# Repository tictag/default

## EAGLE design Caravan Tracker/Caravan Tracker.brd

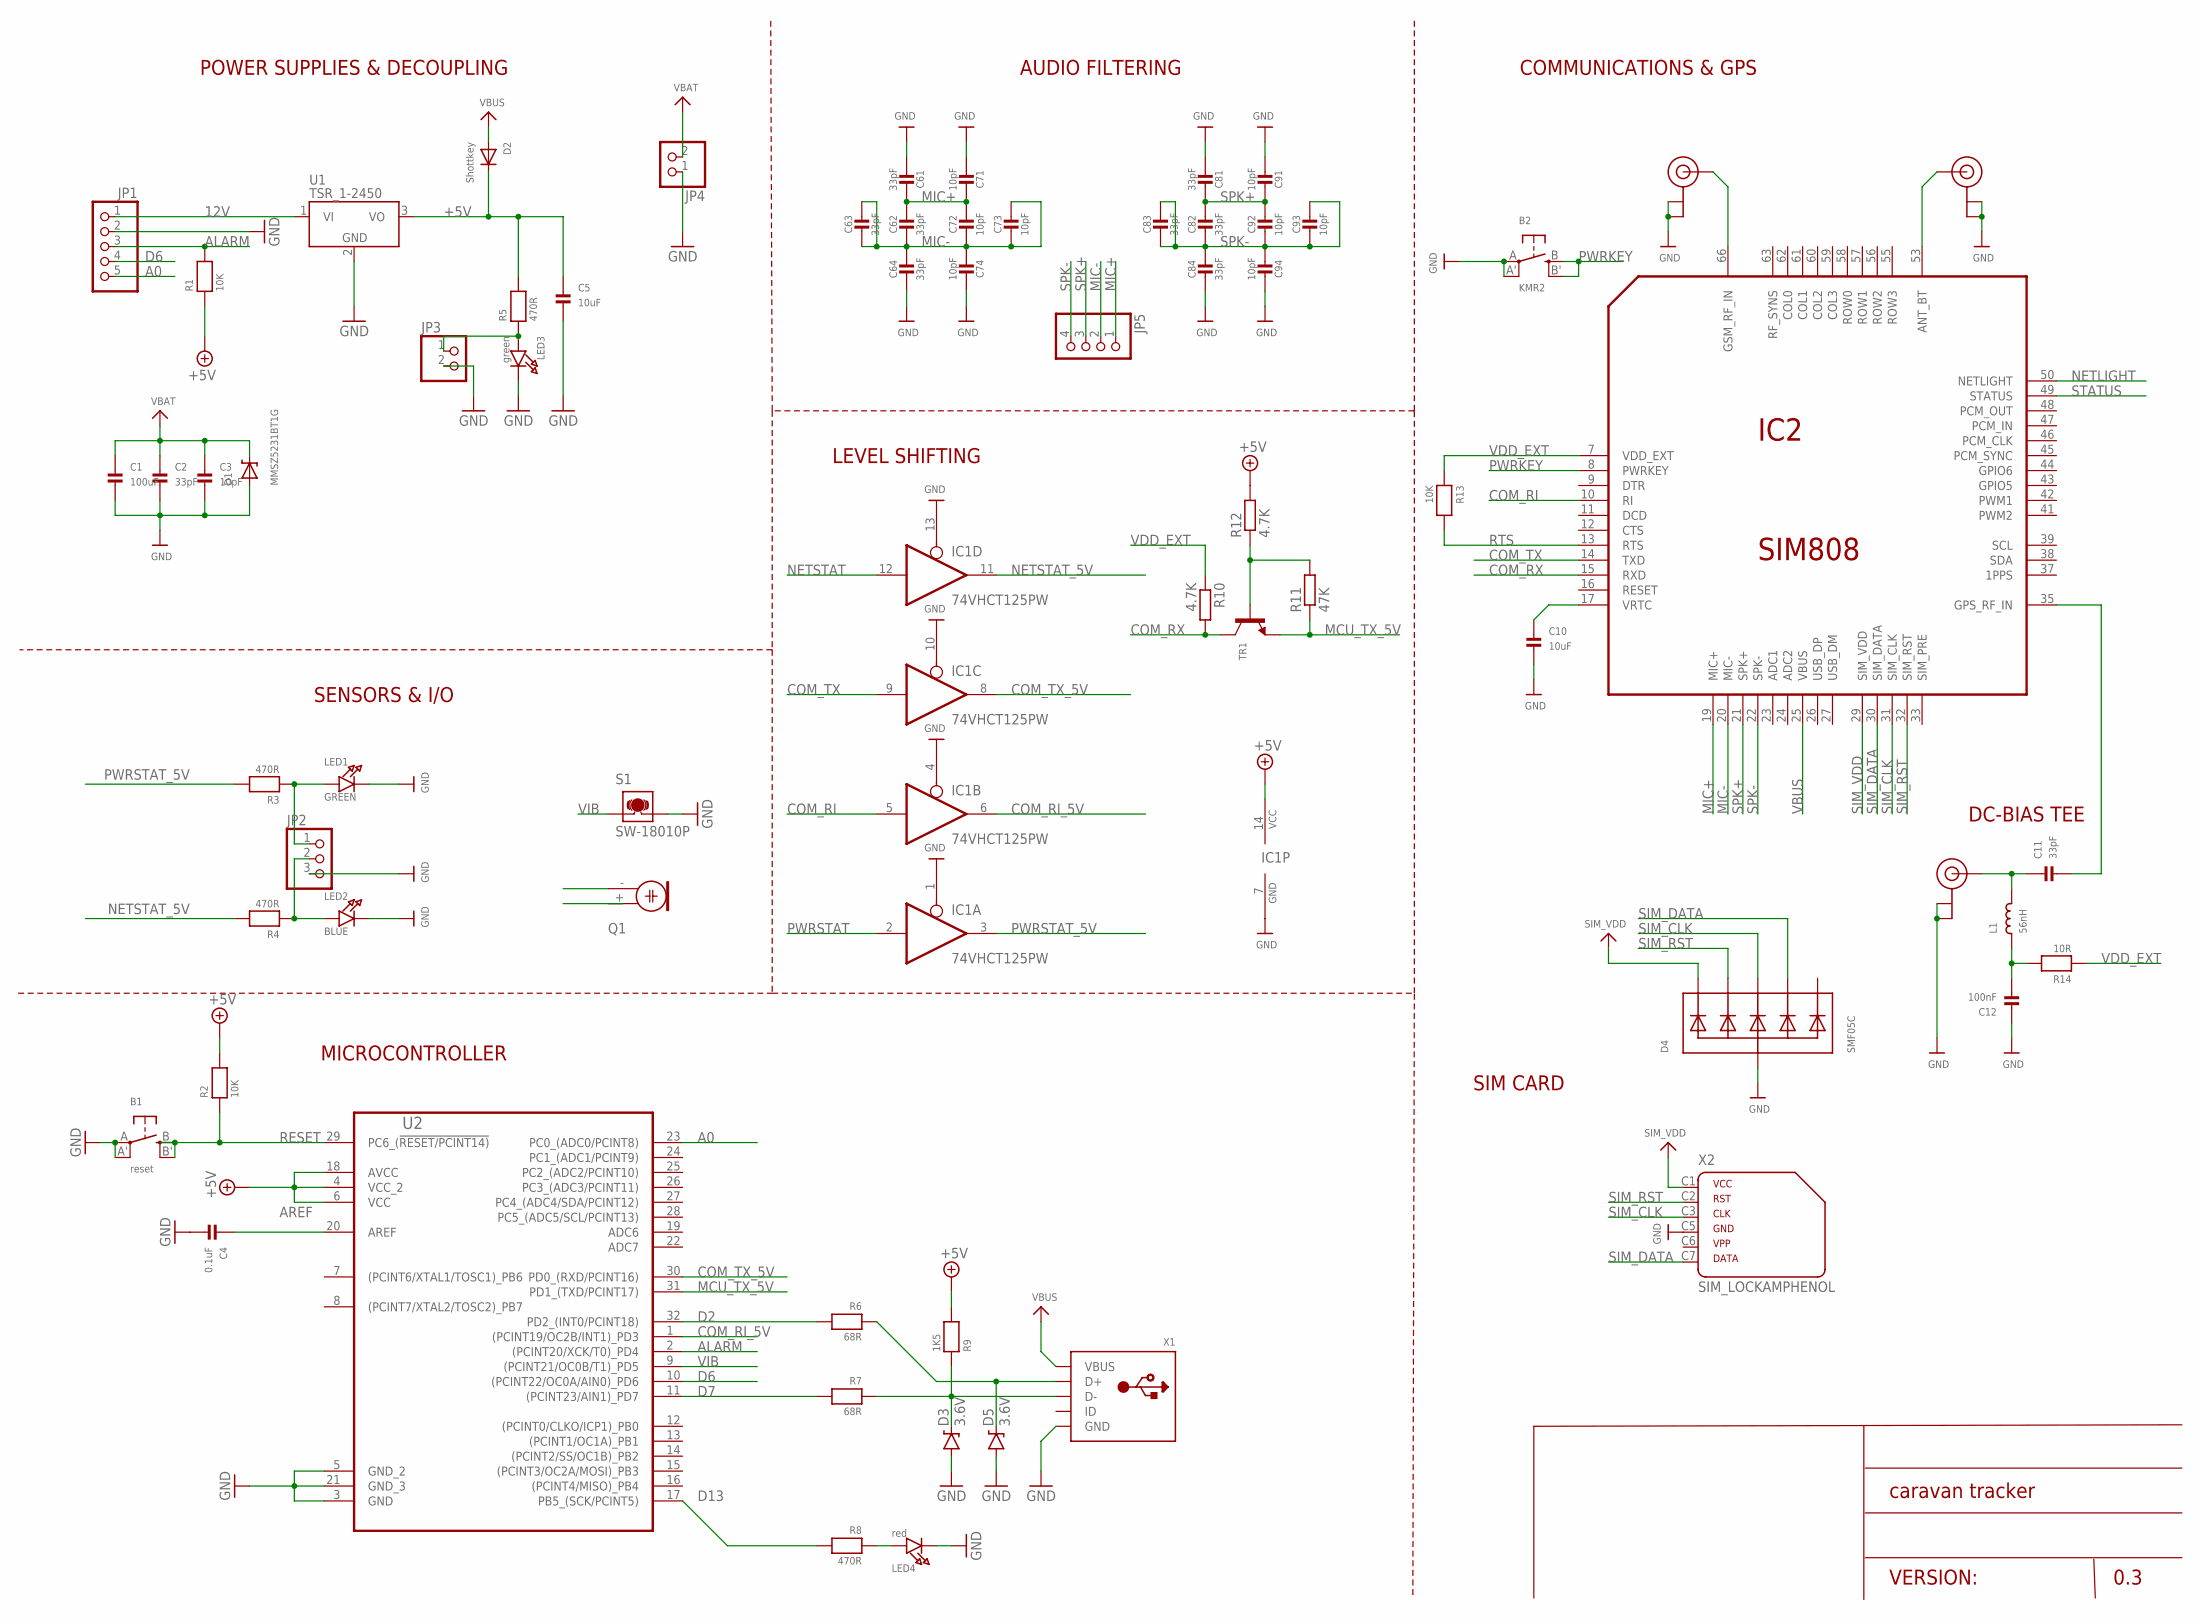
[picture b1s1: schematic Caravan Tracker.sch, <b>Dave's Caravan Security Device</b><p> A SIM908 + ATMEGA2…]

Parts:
B1: reset; BTN_KMR2_4.6X2.8
B2: KMR2; BTN_KMR2_4.6X2.8
C1: 100uF; 1206
C2, C11: 33pF; 0805
C3: 10pF; 0805
C4: 0.1uF; 0603
C5: 10uF; 0603
C6, C8: 33pF; RESPACK_4X0603
C7, C9: 10pF; RESPACK_4X0603
C10: 10uF; 0805
C12: 100nF; 0805
D1: MMSZ5231BT1G; SOD-123
D2: Shottkey; SOD-123
D3, D5: 3.6V; SOD-323
D4: SMF05C; SOT363
IC1: 74VHCT125PW; TSSOP14
IC2: SIM808
JP1: HEADER-1X5ROUND; 1X05_ROUND
JP2: HEADER-1X3ROUND; 1X03_ROUND
JP3: HEADER-1X2ROUND; 1X02_ROUND
JP4: JST_2PIN; JSTPH2
JP5: HEADER-1X4ROUND; 1X04_ROUND
L1: 56nH; _0805
LED1: GREEN; CHIPLED_0805_NOOUTLINE
LED2: BLUE; CHIPLED_0805_NOOUTLINE
LED3: green; CHIPLED_0805_NOOUTLINE
LED4: red; CHIPLED_0805_NOOUTLINE
Q1: ELECTRET; 9.7ELECTRET
R1, R2, R13: 10K; 0603
R3, R4, R5, R8: 470R; 0603
R6, R7: 68R; 0603
R9: 1K5; 0603
R10, R12: 4.7K; R0603
R11: 47K; R0603
R14: 10R; _0805
S1: SW-18010P
TR1: TRANSISTOR_NPN; SOT23-R
U1: TSR_1-2450; TSR-1
U2: ATMEGA328-AU; QFP80P900X900X120-32N
U$1: U.FL (GPS); U.FL
U$2, U$3: U.FL
X1: USBMICRO_20329; 4UCONN_20329
X2: SIM_LOCKAMPHENOL; C707_10M006_512_2

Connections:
12V: JP1.1, U1.1 (VI)
+5V: C5.1, D2.C, IC1.14 (VCC), R1.1, R2.2, R5.2, R9.2, R12.2, U1.3 (VO), U2.4 (VCC_2), U2.6 (VCC), U2.18 (AVCC)
A0: JP1.5, U2.23 (PC0_(ADC0/PCINT8))
ALARM: JP1.3, R1.2, U2.2 ((PCINT20/XCK/T0)_PD4)
ANT_BT: IC2.53 (ANT_BT), U$3.3 (SIGNAL)
AREF: C4.1, U2.20 (AREF)
COM_RI: IC1.5 (I), IC2.10 (RI)
COM_RI_5V: IC1.6 (O), U2.1 ((PCINT19/OC2B/INT1)_PD3)
COM_RX: IC2.15 (RXD), R10.2, TR1.3 (C)
COM_TX: IC1.9 (I), IC2.14 (TXD)
COM_TX_5V: IC1.8 (O), U2.30 (PD0_(RXD/PCINT16))
D2: R6.2, U2.32 (PD2_(INT0/PCINT18))
D6: JP1.4, U2.10 ((PCINT22/OC0A/AIN0)_PD6)
D7: R7.2, U2.11 ((PCINT23/AIN1)_PD7)
D13: R8.2, U2.17 (PB5_(SCK/PCINT5))
GND: B1.A, B1.A' (P1), B2.A, B2.A' (P1), C1.2, C2.2, C3.2, C4.2, C5.2, C6.5 (2), C6.8 (2), C7.4 (1), C7.8 (2), C8.5 (2), C8.8 (2), C9.4 (1), C9.8 (2), C10.2, C12.1, D1.A, D3.A, D4.2 (A), D5.A, IC1.1 (OE), IC1.4 (OE), IC1.7 (GND), IC1.10 (OE), IC1.13 (OE), IC2.1 (GND), IC2.2 (GND), IC2.3 (GND), IC2.18 (GND), IC2.28 (GND), IC2.34 (GND), IC2.36 (GND), IC2.40 (GND), IC2.51 (GND), IC2.52 (GND), IC2.54 (GND), IC2.64 (GND), IC2.65 (GND), IC2.67 (GND), IC2.68 (GND), JP1.2, JP2.3, JP3.2, JP4.1, LED1.C, LED2.C, LED3.C, LED4.C, S1.1, U1.2 (GND), U2.3 (GND), U2.5 (GND_2), U2.21 (GND_3), U$1.1 (GND), U$1.2 (GND), U$2.1 (GND), U$2.2 (GND), U$3.1 (GND), U$3.2 (GND), X1.BASE@1 (GND), X1.BASE@2 (GND), X1.GND, X1.SPRT@1 (GND), X1.SPRT@2 (GND), X1.SPRT@3 (GND), X1.SPRT@4 (GND), X2.C5 (4)
GSM_RF_IN: IC2.66 (GSM_RF_IN), U$2.3 (SIGNAL)
MCU_TX_5V: R11.1, TR1.2 (E), U2.31 (PD1_(TXD/PCINT17))
MIC+: C6.1, C6.2 (1), C7.1, C7.2 (1), IC2.19 (MIC+), JP5.1
MIC-: C6.3 (1), C6.4 (1), C6.6 (2), C6.7 (2), C7.3 (1), C7.5 (2), C7.6 (2), C7.7 (2), IC2.20 (MIC-), JP5.2, Q1.- (1)
unnamed: LED4.A, R8.1
unnamed: JP2.2, LED2.A, R4.1
unnamed: D5.C, R6.1, X1.D+
unnamed: JP2.1, LED1.A, R3.1
unnamed: D3.C, R7.1, R9.1, X1.D-
unnamed: JP3.1, LED3.A, R5.1
unnamed: C12.2, L1.1, R14.2
unnamed: R11.2, R12.1, TR1.1 (B)
unnamed: C11.1, L1.2, U$1.3 (SIGNAL)
unnamed: C11.2, IC2.35 (GPS_RF_IN)
unnamed: C10.1, IC2.17 (VRTC)
NETLIGHT: IC2.50 (NETLIGHT)
NETSTAT: IC1.12 (I)
NETSTAT_5V: IC1.11 (O), R4.2
PWRKEY: B2.B (S), B2.B' (S1), IC2.8 (PWRKEY)
PWRSTAT: IC1.2 (I)
PWRSTAT_5V: IC1.3 (O), R3.2
RESET: B1.B (S), B1.B' (S1), R2.1, U2.29 (PC6_(!RESET/PCINT14))
RTS: IC2.13 (RTS), R13.2
SIM_CLK: D4.4 (C3), IC2.31 (SIM_CLK), X2.C3 (3)
SIM_DATA: D4.5 (C4), IC2.30 (SIM_DATA), X2.C7 (6)
SIM_RST: D4.3 (C2), IC2.32 (SIM_RST), X2.C2 (2)
SIM_VDD: D4.1 (C1), IC2.29 (SIM_VDD), X2.C1 (1)
SPK+: C8.1, C8.2 (1), C9.1, C9.2 (1), IC2.21 (SPK+), JP5.3
SPK-: C8.3 (1), C8.4 (1), C8.6 (2), C8.7 (2), C9.3 (1), C9.5 (2), C9.6 (2), C9.7 (2), IC2.22 (SPK-), JP5.4
STATUS: IC2.49 (STATUS)
VBAT: C1.1, C2.1, C3.1, D1.C, IC2.4 (VBAT), IC2.5 (VBAT), IC2.6 (VBAT), JP4.2
VBUS: D2.A, IC2.25 (VBUS), X1.VBUS
VDD_EXT: IC2.7 (VDD_EXT), R10.1, R13.1, R14.1
VIB: S1.2, U2.9 ((PCINT21/OC0B/T1)_PD5)

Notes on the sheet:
MICROCONTROLLER
POWER SUPPLIES & DECOUPLING
COMMUNICATIONS & GPS
SIM CARD
AUDIO FILTERING
LEVEL SHIFTING
SENSORS & I/O
VERSION:
0.3
DC-BIAS TEE

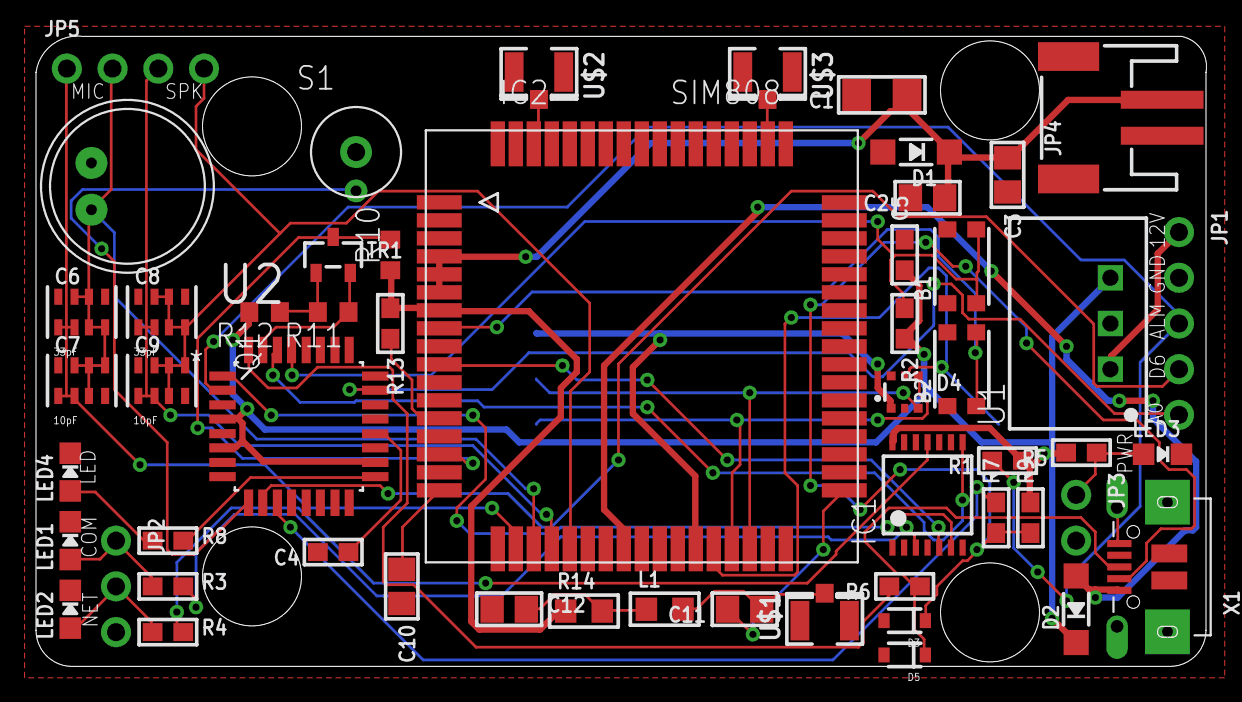
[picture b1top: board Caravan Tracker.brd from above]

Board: 2 copper layers, 65.0 x 35.0 mm, 55 parts (1 on the bottom side), 46 nets.

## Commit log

2015-05-28 :octocat: Added .gitattributes & .gitignore files
2015-07-28 Caravan Tracker v0.3
    Updated USB design (including zeners per V-USB hardware spec)

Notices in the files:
parts and their libraries:
microbuilder: This work is placed in the public domain, and may be freely used for commercial and non-commercial work with the following conditions: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
SparkFun-DiscreteSemi: Licensing: Creative Commons ShareAlike 4.0 International - https://creativecommons.org/licenses/by-sa/4.0
